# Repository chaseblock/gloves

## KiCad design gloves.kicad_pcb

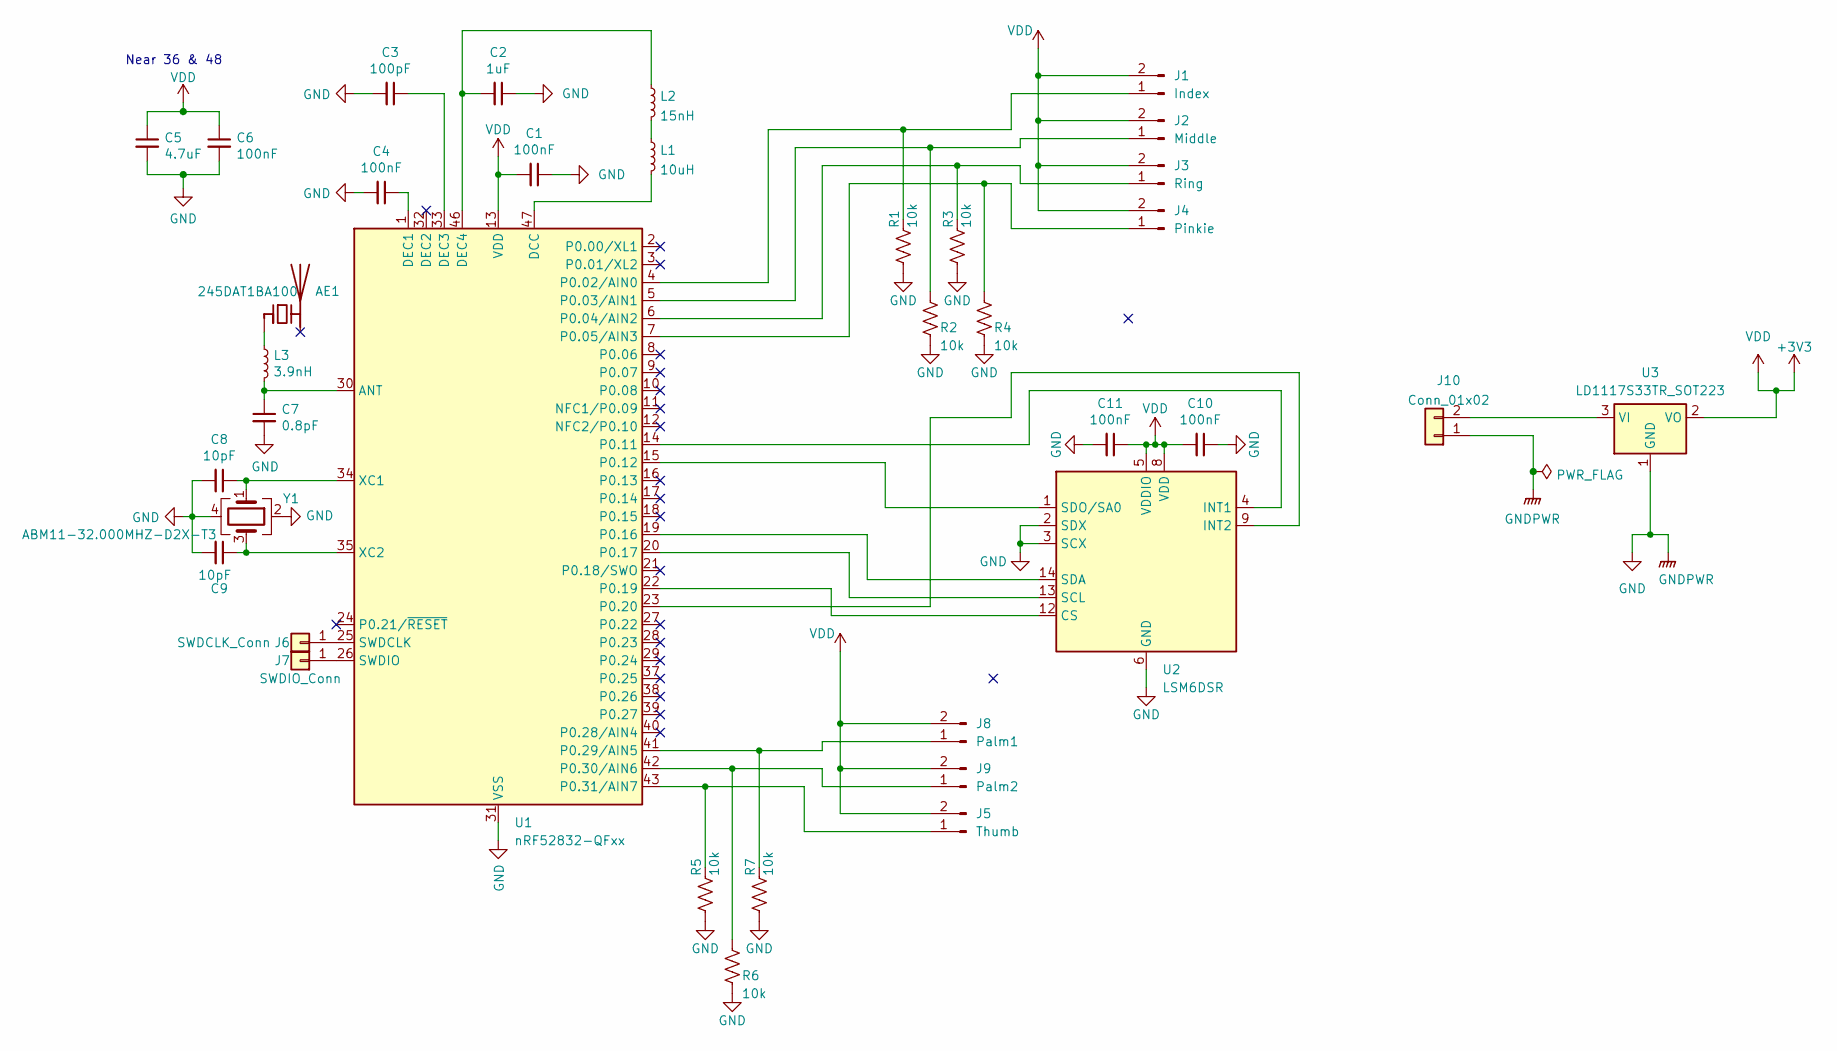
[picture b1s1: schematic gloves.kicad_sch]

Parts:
AE1: 245DAT1BA100; Johanson_2450AT18x100; Mouser Link n/a
C1, C4, C6, C10, C11: 100nF; C_0402_1005Metric
C2: 1uF; C_0402_1005Metric
C3: 100pF; C_0402_1005Metric
C5: 4.7uF; C_0402_1005Metric
C7: 0.8pF; C_0402_1005Metric
C8, C9: 10pF; C_0402_1005Metric
J1: Index; SolderWire-0.1sqmm_1x02_P3.6mm_D0.4mm_OD1mm
J2: Middle; SolderWire-0.1sqmm_1x02_P3.6mm_D0.4mm_OD1mm
J3: Ring; SolderWire-0.1sqmm_1x02_P3.6mm_D0.4mm_OD1mm
J4: Pinkie; SolderWire-0.1sqmm_1x02_P3.6mm_D0.4mm_OD1mm
J5: Thumb; SolderWire-0.1sqmm_1x02_P3.6mm_D0.4mm_OD1mm
J6: SWDCLK_Conn; SolderWirePad_1x01_SMD_1x2mm
J7: SWDIO_Conn; SolderWirePad_1x01_SMD_1x2mm
J8: Palm1; SolderWire-0.1sqmm_1x02_P3.6mm_D0.4mm_OD1mm
J9: Palm2; SolderWire-0.1sqmm_1x02_P3.6mm_D0.4mm_OD1mm
J10: Conn_01x02; PinHeader_1x02_P2.54mm_Horizontal
L1: 10uH; L_0603_1608Metric
L2: 15nH; L_0402_1005Metric
L3: 3.9nH; L_0402_1005Metric
R1, R2, R3, R4, R5, R6, R7: 10k; R_0402_1005Metric_Pad0.72x0.64mm_HandSolder
U1: nRF52832-QFxx; QFN-48-1EP_6x6mm_P0.4mm_EP4.6x4.6mm
U2: LSM6DSR; LGA-14_3x2.5mm_P0.5mm_LayoutBorder3x4y
U3: LD1117S33TR_SOT223; SOT-223-3_TabPin2
Y1: ABM11-32.000MHZ-D2X-T3; Crystal_SMD_Abracon_ABM10-4Pin_2.5x2.0mm

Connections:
+3V3: C1.2, C5.1, C6.1, C10.2, C11.1, J1.2, J2.2, J3.2, J4.2, J5.2, J8.2, J9.2, U1.13 (VDD), U1.36 (VDD), U1.48 (VDD), U2.5 (VDDIO), U2.8 (VDD), U3.2 (VO)
GND: C1.1, C2.1, C3.2, C4.2, C5.2, C6.2, C7.2, C8.2, C9.2, C10.1, C11.2, J10.1, R1.2, R2.2, R3.2, R4.2, R5.2, R6.2, R7.2, U1.31 (VSS), U1.45 (VSS), U1.49 (VSS), U2.2 (SDX), U2.3 (SCX), U2.6 (GND), U2.7 (GND), U3.1 (GND), Y1.2, Y1.4
unnamed: AE1.1 (FEED), L3.1
unnamed: J1.1, R1.1, U1.4 (P0.02/AIN0)
unnamed: J2.1, R2.1, U1.5 (P0.03/AIN1)
unnamed: J3.1, R3.1, U1.6 (P0.04/AIN2)
unnamed: J4.1, R4.1, U1.7 (P0.05/AIN3)
unnamed: J5.1, R5.1, U1.43 (P0.31/AIN7)
unnamed: J6.1, U1.25 (SWDCLK)
unnamed: J7.1, U1.26 (SWDIO)
unnamed: J8.1, R7.1, U1.41 (P0.29/AIN5)
unnamed: J9.1, R6.1, U1.42 (P0.30/AIN6)
unnamed: J10.2, U3.3 (VI)
unnamed: L1.1, L2.2
unnamed: C7.1, L3.2, U1.30 (ANT)
unnamed: L1.2, U1.47 (DCC)
unnamed: C4.1, U1.1 (DEC1)
unnamed: C3.1, U1.33 (DEC3)
unnamed: C2.2, L2.1, U1.46 (DEC4)
unnamed: U1.14 (P0.11), U2.4 (INT1)
unnamed: U1.15 (P0.12), U2.1 (SDO/SA0)
unnamed: U1.19 (P0.16), U2.14 (SDA)
unnamed: U1.20 (P0.17), U2.13 (SCL)
unnamed: U1.22 (P0.19), U2.12 (CS)
unnamed: U1.23 (P0.20), U2.9 (INT2)
unnamed: C8.1, U1.34 (XC1), Y1.1
unnamed: C9.1, U1.35 (XC2), Y1.3

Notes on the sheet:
Near 36 & 48

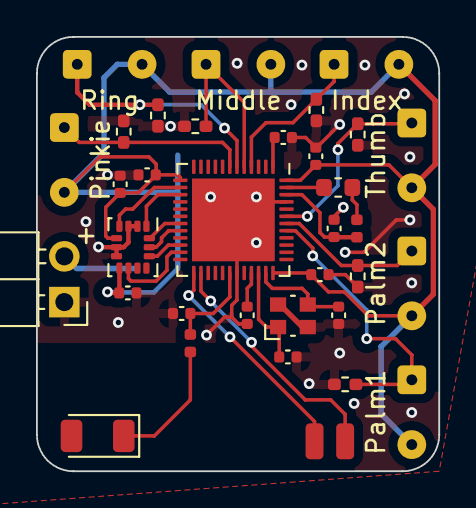
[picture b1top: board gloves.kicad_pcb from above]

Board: 2 copper layers, 22.4 x 24.1 mm, 36 parts (1 on the bottom side), 27 nets.

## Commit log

2024-03-20 Design
